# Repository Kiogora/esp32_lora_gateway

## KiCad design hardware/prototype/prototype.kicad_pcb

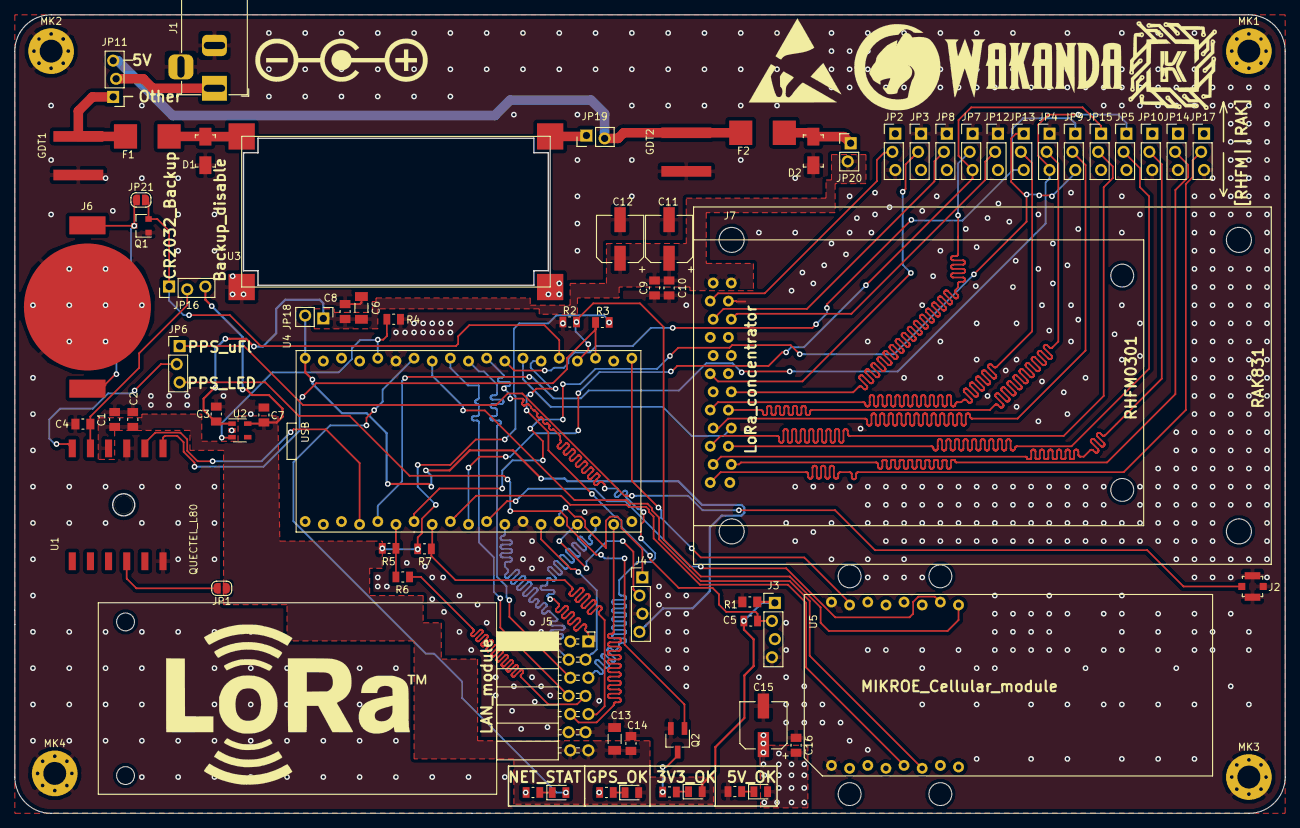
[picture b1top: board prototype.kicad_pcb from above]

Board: 2 copper layers, 177.8 x 111.8 mm, 76 parts (0 on the bottom side), 62 nets.

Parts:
C1, C4, C5, C7, C8, C10, C14, C16: 0.1uF; C_0805_2012Metric_Pad1.15x1.50mm_HandSolder
C2: 10uF; C_0805_2012Metric_Pad1.15x1.50mm_HandSolder
C3: 1uF; C_0805_2012Metric_Pad1.15x1.50mm_HandSolder
C6, C13: 10uF; C_1206_3216Metric_Pad1.24x1.80mm_HandSolder
C9: 100pF; C_0805_2012Metric_Pad1.15x1.50mm_HandSolder
C11, C12, C15: 220uF; CP_Elec_6.3x5.8
D1, D2: D_TVS; DO-214AC
D3, D4, D5, D6: LED; LED_0805_2012Metric_Pad0.97x1.50mm_HandSolder
F1, F2: Fuse_Small; 461_series_Telelink
GDT1, GDT2: GDT-; SL1411A075-SM
J1: Jack-DC; BarrelJack_Horizontal
J2: 0734120114; Molex_734120114_UMC_RF_CONN_Vertical
J3, J4: Conn_01x04; PinHeader_1x04_P2.54mm_staggered_Vertical
J5: Conn_02x07_Odd_Even; lan_waveshare_8720
J6: Battery-holder; BAT-HLD-001-xx-OTL
J7: Conn_02x12_Odd_Even; Hybrid_concentrator
JP1, JP21: SolderJumper_2_Open; SolderJumper-2_P1.3mm_Open_RoundedPad1.0x1.5mm
JP2, JP3, JP4, JP5, JP7, JP8, JP9, JP10, JP11, JP12, JP13, JP14, JP15, JP16, JP17: Jumper_NC_Dual; PinHeader_1x03_P2.54mm_staggered_Vertical
JP6: Jumper_3_Open; PinHeader_1x03_P2.54mm_staggered_Vertical
JP18, JP19, JP20: Jumper; PinHeader_1x02_P2.54mm_staggered_Vertical
MK1, MK2, MK3, MK4: Mounting_Hole_PAD; MountingHole_3.2mm_M3_Pad_Via
Q1: Si2323; SOT-23
Q2: DTC143Z; SC-59_Handsoldering
R1, R2, R3: 10k; R_0805_2012Metric
R4, R5: 4.7k; R_0805_2012Metric
R6: 33R; R_0805_2012Metric
R7: 1.5k; R_0805_2012Metric
R8: 110R; R_0805_2012Metric
R9, R10: 130R; R_0805_2012Metric
R11: 300R; R_0805_2012Metric
U1: QUECTEL_L80; QUECTEL_L80-M39
U2: TLV71333PDBV; SOT-23-5
U3: LM2596_MODULE
U4: DevkitC; ESP32_DEVKITC
U5: MIKROE_3G_CLICK; MIKROE_UG95

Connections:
/3: J7.3, JP2.2
/3V3_REF: U4.20, U5.7
/5: J7.5, JP8.2
/5v_rail: F2.1, GDT2.1, JP11.3, JP19.2
/6: J7.6, JP12.2
/11: J7.11, JP3.2
/12v_rail: F1.1, GDT1.1, JP11.1
/14: J7.14, JP7.2
/15: J7.15, JP13.2
/16: J7.16, JP4.2
/17: J7.17, JP9.2
/19: J7.19, JP15.2
/20: J7.20, JP5.2
/21: J7.21, JP10.2
/22: J7.22, JP14.2
/23: J7.23, JP17.2
/BRD_GPS_1PPS: JP6.2, U1.6
/BRD_GPS_RX: R3.2, U1.1, U4.22
/BRD_GPS_TX: U1.2, U4.4
/BRD_GPS_VBCKUP: C4.2, JP16.2, U1.5
/CELLULAR_5V: C3.1, C6.1, C8.1, C9.1, C10.1, C11.1, C12.1, C15.1, C16.1, D6.2, J7.1, J7.2, JP18.1, JP20.2, U2.1, U5.15
/CONTROLLER_RX: J4.1, U4.15
/CONTROLLER_TX: J4.2, U4.16
/CSN: JP9.3, JP13.1, U4.7
/ESP32_5v: J4.4, JP18.2, U4.38
/GLOBAL_3V3: C1.1, C2.1, C5.1, C7.1, C13.1, C14.1, D3.2, D5.2, J3.1, J5.13, J5.14, JP1.1, JP16.3, R1.1, R3.1, R5.1, R7.1, U1.4, U2.5
/GSM_RX: U4.9, U5.12
/GSM_TX: U4.31, U5.11
/MISO: JP9.1, JP13.3, U4.27
/MOSI: J7.18, U4.26
/NETWORK_STATUS: D4.2, U4.32
/PHY_POWER_EN: R4.1, U2.3, U4.34
/PPS_VISUAL: JP6.3, Q2.1
/PWR_KEY: U4.11, U5.2
/Power_Input: J1.1, JP11.2
/RESET: JP7.3, JP15.1, U4.10
/RMII-RX0: J5.5, U4.28
/RMII_CRS_DV: J5.8, U4.30
/RMII_MDC: J5.10, U4.18
/RMII_MDIO: J5.9, R7.2, U4.8
/RMII_REFOSC_nINT: R5.2, R6.1, U4.6
/RMII_RX1: J5.6, U4.29
/RMII_TX0: J5.4, U4.12
/RMII_TX1: J5.1, U4.17
/RMII_TX_EN: J5.3, U4.14
/SCK: JP4.3, JP5.1, U4.5
/STATUS: R2.1, U4.23, U5.1
/TEMP_DATA: J3.2, R1.2, U4.25
/V_BCKUP: JP16.1, JP21.2, Q1.2, U4.24
GND: C1.2, C2.2, C3.2, C4.1, C5.2, C6.2, C7.2, C8.2, C9.2, C10.2, C11.2, C12.2, C13.2, C14.2, C15.2, C16.2, D1.2, D2.2, GDT1.2, GDT2.2, J1.2, J1.3, J2.1, J3.4, J4.3, J5.11, J5.12, J6.2, J7.4, JP2.3, JP3.1, JP4.1, JP7.1, JP8.1, JP10.3, JP12.1, JP14.3, JP17.3, MK1.1, MK2.1, MK3.1, MK4.1, Q1.1, Q2.2, R2.2, R4.2, R9.1, R10.1, R11.1, U1.3, U1.12, U2.2, U3.2, U3.4, U4.13, U4.19, U4.33, U5.8, U5.16
unnamed: D1.1, F1.2, U3.1
unnamed: D2.1, F2.2, JP20.1
unnamed: D3.1, R8.2
unnamed: D4.1, R9.2
unnamed: D5.1, R10.2
unnamed: D6.1, R11.2
unnamed: J2.2, JP6.1
unnamed: J5.7, R6.2
unnamed: J6.1, JP21.1, Q1.3
unnamed: JP1.2, U1.10
unnamed: JP19.1, U3.3
unnamed: Q2.3, R8.1

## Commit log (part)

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2017-12-30 Create TODO
    Add development procedure
2017-12-30 Update TODO
2017-12-30 Update agc_fw.var
    Minor changes
2017-12-30 Update arb_fw.var
    Minor changes
2017-12-30 Update loragw_aux.c
    Minor typographic changes
2017-12-30 Update loragw_fpga.c
    Minor typographic changes
2017-12-30 Update loragw_gps.c
    Minor typographical changes
2017-12-30 Update loragw_radio.c
    Minor typographical changes
2017-12-30 Update loragw_reg.c
    Minor typographical changes.
2017-12-30 Update loragw_spi.native.c
    Minor typographical changes.
2017-12-31 Semi-port spi driver to the esp32. Not yet tested
2017-12-31 Delete loragw_spi.ftdi.c
    Delete this driver for the freestanding ESP32 environment.
2017-12-31 Add esp32 template project for porting
2018-01-01 Add intermediary files
2018-01-03 Complete and approve unit test of SPI write operation
2018-01-07 Complete porting of loragw_spi component
2018-01-14 Complete loragw_reg component porting and tests
2018-01-14 Convert the esp32 from from a unit test app to an actual project
2018-01-14 Successfully ran loragw_hal test under console
2018-01-15 Complete SPI stress test porting
2018-01-15 Modify cmdline flashing baudrate to 921kbaud
2018-01-16 Add LBT test
2018-01-17 Rearrange folders and semiport tx test
2018-01-17 Set c_cpp_properties.json to use IDF_PATH variable instead of full path
2018-01-20 Modify readme
2018-01-24 Add menuconfig option to test scripts
2018-01-26 Add iperf TCP performance tests
2018-01-26 Add details that identify iperf tests done were done over Wifi
2018-01-27 Update loragw_reg.c
    1. Add explicit calls to lgw_disconnect in lgw_connect in case of error.
    2. As a device is configured and host added during this operations, any error doesnt allow us to use the spi host.
    3. We need to free this within the API so that it is invisible to the API user.
2018-01-27 Rmove lgw_stop()
    1. No need to call lgw_stop if lgw_start is unsuccessful. Beats logic to so so.
    2. The lgw_stop is implemented within the API making it invisible to the API user
2018-01-27 Retype using consistent API
    1. Use the higher abstraction lgw_disconnet inside of lgw_close as lgw_connect was in the beginning of the document.
2018-01-27 Update cmd_loragw_cal.c
    1. Delete call to lgw_disconnect()
    2. This would rather be called at the beginning of lgw_connect in order to catch the exception and free up resources before reallocation.
2018-01-27 Delete calls to lgw_close() in continuous_tx util
    See previous commits for reasons
2018-01-27 Add concentrator restart if started
    1. Added a call to lgw_stop() in lgw_start() to catch exceptions when we try to start the concentrator when already started.
    2. Such an example is when doing testing with a menu such as normal of cmdline tests.
    3. Also there are times when we may want to restart the concentrator, we can do this by calling lgw_connect()
    4. How would this fare up when a restart happens while data is still in transit via DMA?
2018-01-28 Remove statement with little affect.
2018-01-29 Find a standard way of handling errors during and post concentrator connection
    1. Errors during connects are handled by the API, no need to call a disconnect() or stop() if a return value indicates error.
    2. Errors after succesful connect are the responsibility of the programmer using the API. One may disconnect or not disconnect.
2018-01-29 Complete retesting the tests
2018-02-05 Initial TTN gateway connector code
    1. Add code to connect to the gateway to a ttn test broker on local host on network.
    2. protobuf-c is directly ported from the online repo.
    3. protoc-c compiler is not used and any such code generation shall be done on the host not target.
    4. TODO - Port the packet forwarder and test with ttn. Port nanopb to the platform. Perform comparisons.
2018-02-13 Add preliminary files for porting of LoRanet/packet fowarder
2018-02-15 Add parson test files to command line tests
    1.This first loads a fatfs image for the command line then when parson is run, a spiffs image is loaded.
    2. Check why the spiffs image is not mounting. Gives error "Not a filesystem".
2018-02-21 Add GPS helper functions
    1. These are primarily for testing ublox GPS.
    2. They should be fully ported by using only posix compliant functions, no GNU_SOURCE
    3. After testing and this giving a nice refrence, we will rename this source and header files to loragw_ublox_gps.*
    4. Finally port Quectel GPS chips
2018-02-22 Multiple commits in this commmit
    1. Reverted parson_test to the original without malloc checks.
    2. Completed loragw_gps. Removed timezone variable as the TZ variable will not be set, even when using SNTP.This above will set the time to UTC from NTP servers avoiding subrtraction of the timezone 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
2018-02-22 Succesfully ported GPS test
    1. The GPS sync was obtained but NMEA message and thus coordinates was not obtained.
    2. Recheck that NMEA-RMC messages are enabled via serial port.
    3. In future, for Quectel GPS's, work with NMEA-ZDA to obtain UTC time.
2018-02-22 Add Fletcher-16 UBX message checksum calculator
    1. Originally from https://gist.github.com/tomazas/3ab51f91cdc418f5704d
2018-02-22 Enable NMEA RMC sentences output on serial
2018-02-23 Complete Ublox GPS test
2018-02-23 Allow overriding of spiffs image on command line
2018-02-23 Add GCC debug switch case(-g) in makefile
    1. This provides symbols for valgrind to backtrace.
    2. May solve reason we cant unpack SPIFFS image read from esp32 flash.
2018-02-24 Add deprendency to mkspiffs build system
    1.The target binary will rebuild if any source file is modified.
    2. There was a lack of dependency like this prior.
2018-02-24 Correct error preventing mkspiffs unpacking
    1. The unpacking of current directory . of a folder always returned a NULL.
    2. Add necessary check for NULL pointer return value and ignore the "." file.
    3. Sample output:
    >>> spiffs image content:/.
    >>> Failed to open file, is this the current folder representation "."? Ignoring...
    >>> /. > ./foo/. size: 0 Bytes#
2018-02-24 Ported packet logger utility
    1. The rollover time is not accurate when counting on the ESP32.
    2. It is best if such timekeep details are kept by a real time clock and a GPS used for synchronisation.
    3. The timespec structure was not used, replaced with timeval instead. Couldnt find compatible clock_gettime() func.
    4. Unix system function access was not used for checking file permissions. Incompatible.
    5. The logging, readback and unpacking works very well.
    6. No memory leaks from parson so far.
2018-02-24 Correct timing
    1. Eliminate wrong parameter casting. The rollover time was being cast to uint8 datatype hence the early close of the write ops.
2018-02-26 Set update of time at start by SNTP protocol
    1.This allows the ESP32 to update its time by SNTP thus giving a relatively accurate UTC timestamp on the logs.
2018-02-27 Add project-local Unity test framework
    1. This is from src directory of commit hash 287e076 v2.4.3 of the Unity github repo https://github.com/ThrowTheSwitch/Unity/tree/v2.4.3 .
    2. This would allow running true unit tests within the cmdline tests.
    3. The tests should be ported from ESP-IDF unity tests to project local unity tests.
2018-02-27 Remove host libraries from vscode include path
2018-02-27 Add jitqueue component
2018-03-06 Successfully port UDP packet forwarder
    1. This works very well with the things network
    2. GPS not yet tested.
    3. In future the current times should be made by an external RTC in the case of lack of network access.
    4. In the case (3), the messages should be cached locally in the case of lack of network access.
2018-03-07 Set gateway to obtain MAC dynamically
2018-03-07 Update perf_tests
2018-03-10 Update timersync delay
    1. Reduced the timersync delay from 60sec to 8sec.
    2. The assumption on XTAL precision drift at 20ppm
    was not applicable.
    3. With 8 second delay, the timestamp was nearly accurate to the second.
    4. This should be retested.
2018-03-14 Add PPP support to cmdline sdkconfig
2018-03-14 Add quectel-gsm component
    1. Its use has only been tested standalone outside the project.
    2. The project in its current state throws:
    fatal error: quectel_gsm.h: No such file or directory
2018-03-17 Clean Loragw_spi
    1. Sanitised the log messages for spi component.
    2. Normal messages in this component is given as verbose(ESP_LOGV).
    3. Errors are treated as so.
    4. There may be a need to come up with unified error codes.
2018-03-17 Capitalise log message
2018-03-17 Minor modifications to log statements in reg component
    1. Capitalised all log statements.
    2. Set majority of the log statements to verbose as they are low level.
    3. Log is set to info level only to the reg check/verify function.
2018-03-17 Setup logging in loragw radio component
    1. Set up logging as verbose as this is low level.
    2. Unified error codes would be useful in a production environment.
2018-03-18 Sanitize logging on LBT component
2018-03-19 Sanitize logging on FPGA component
2018-03-19 Sanitize logging in base64 component
2018-03-19 Rename GSM components
2018-03-19 Add logging modification in spi read function.
2018-03-20 Finalise logging on lora pkt forwarder
2018-03-20 Finalise ping command
2018-03-21 Modify ping commmand
    1. Reference actual packet TTL in lwip/opt.h
    2. Remove delay with minimal use from code
2018-03-22 Eliminate brackets around wifi password option
    1. This was caued by the expected string input being defined as var str0
    2. var0 such as str0, int0 means that the option need not be given.
    3. In the case of an open wifi network str0 is appropriate.
    4. Our test AP has a password though.
2018-03-22 Eliminate redundant ap_args variable
2018-03-22 Remove "load firmware" function prototype from cmd_cal to hal component
    1. The prototype was missing from the hal header.
2018-03-22 Finalise logging onspi stress utility
2018-03-22 Finalise porting of logging functions to ESP32 format ESP_LOGx
2018-03-27 Add prototype hardware files
2018-04-02 semi-finaliseprototype gateway design
2018-04-02 Add missing footprints
    1. Think about lightning protection and use of GDTs and TVSs
    2. Combine the various board and peripheral libraries into a single unified component.
    3. The component should have mounting holes suitable for standoffs and cable ties.
2018-04-22 Complete schematic less mikroe ug95 footprint
2018-04-23 Complete schematic design less footprint asignment completion
2018-04-26 Complete schematic and component footpint selection
2018-04-29 Complete PCB layout
2018-04-29 Modify PCB layout
2018-05-04 Complete PCB design, BOM generation and gerber generation
2018-06-03 Move flash partitions csv to dedicated partitions folder
2018-06-03 Rename esp32_port folder to firmware
2018-06-04 Port working of loragw GPS test
    1. Swapped RX and TX in code due to errata. This means TX cant work asit is on SVP which is input only.
    2. Set the uart reads to happen every one second.
2018-06-04 Add prototype errata
2018-06-04 Modify errata
2018-06-04 Move errata folder to top level
2018-06-04 Remove duplicate files
2018-06-04 Remove unneeded files
2018-06-05 Add issue on booting to errata
2018-06-07 Add errata on cellular latency exceeding the 1 second RX1 window
2018-06-07 Correct errata on cellular latency.
2018-06-07 Add payload decryption script for post packet logger analysis
2018-06-07 Correct readme
2018-06-07 Remove unneeded folders
2018-06-07 Remove unneeded folder
2018-06-07 Remove TODO folder
2018-06-07 Remove scripts and sdkconfig files
    1. Removed the above because the difference between main and cmdline_tests is the partition table.
    2. This can be modified by having the user choose in menuconfig, which is mandatory either-way.
2018-06-07 Correct typo in prototyping notes
2018-06-08 Add test information in README
2018-06-08 Change inline source code formatting from shell to none
2018-06-08 Change formatting in README
2018-06-11 Add more sections to the hardware errata encountered so far
2018-06-14 Add further investigation on spi boot error
2018-06-18 Add images on differences of esp32 core board versions
2018-06-18 Add TVS diode order mistake
2018-06-18 Correct typo
